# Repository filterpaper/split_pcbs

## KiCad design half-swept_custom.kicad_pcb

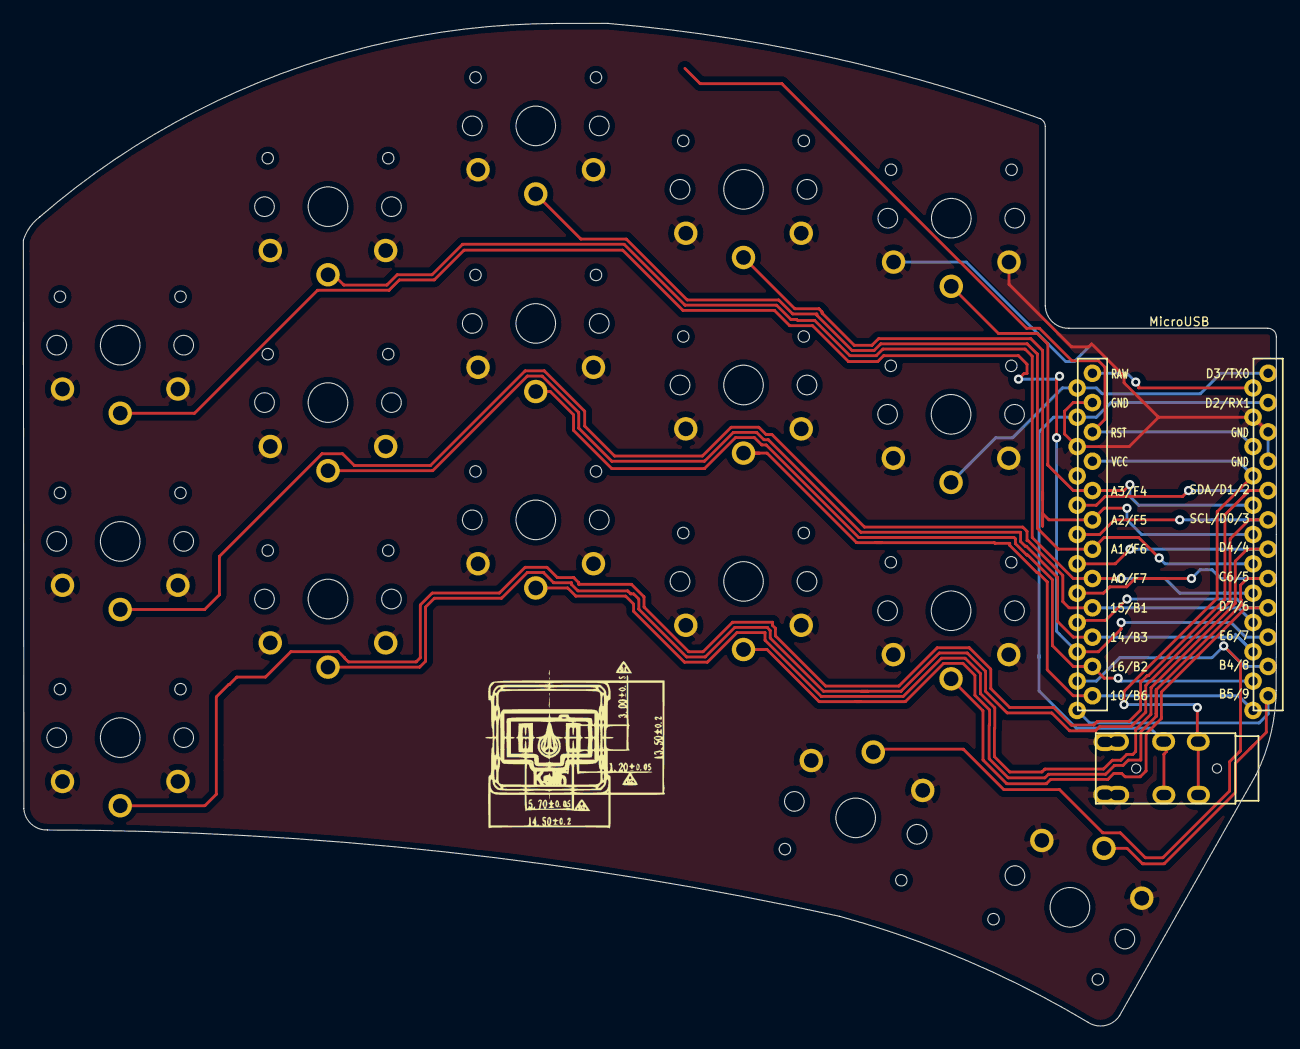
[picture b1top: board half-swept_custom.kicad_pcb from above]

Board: 2 copper layers, 108.6 x 86.9 mm, 19 parts (0 on the bottom side), 20 nets.

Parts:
J2: AudioJack4dpb; TRRS-PJ-DPB2
SW2, SW3, SW4, SW5, SW6, SW8, SW9, SW10, SW11, SW12, SW14, SW15, SW16, SW17, SW18, SW20, SW21: SW_Push; SW_PG1350_rev_DPB
U1: ProMicro-kbd; ProMicro_v2

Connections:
Switch1: SW2.1, U1.10
Switch2: SW3.1, U1.17
Switch3: SW4.1, U1.18
Switch4: SW5.1, U1.19
Switch5: SW6.1, U1.20
Switch6: SW8.1, U1.16
Switch7: SW9.1, U1.15
Switch8: SW10.1, U1.14
Switch9: SW11.1, U1.13
Switch10: SW12.1, U1.1
Switch11: SW14.1, U1.5
Switch12: SW15.1, U1.6
Switch13: SW16.1, U1.7
Switch14: SW17.1, U1.8
Switch15: SW18.1, U1.9
Switch16: SW21.1, U1.11
Switch17: SW20.1, U1.12
Switch18: J2.R1, U1.2
gnd: J2.S, J2.T, SW2.2, SW3.2, SW4.2, SW5.2, SW6.2, SW8.2, SW9.2, SW10.2, SW11.2, SW12.2, SW14.2, SW15.2, SW16.2, SW17.2, SW18.2, SW20.2, SW21.2, U1.3, U1.4, U1.23
vcc: J2.R2, U1.21
